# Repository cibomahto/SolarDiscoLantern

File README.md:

Solar Disco Lantern
===================

A disco twist on the traditional solar lantern, this little guy will light your way at night, and bounce to your music!

An all-analog circuit makes for a low-power and low-cost design.

The solar charging circuit is based on the Kimono Lantern Kit by Akiba:
http://www.tokyohackerspace.org/en/project/kimono-lantern

Designed by Honghong and Matt for Dragon Burn 2014

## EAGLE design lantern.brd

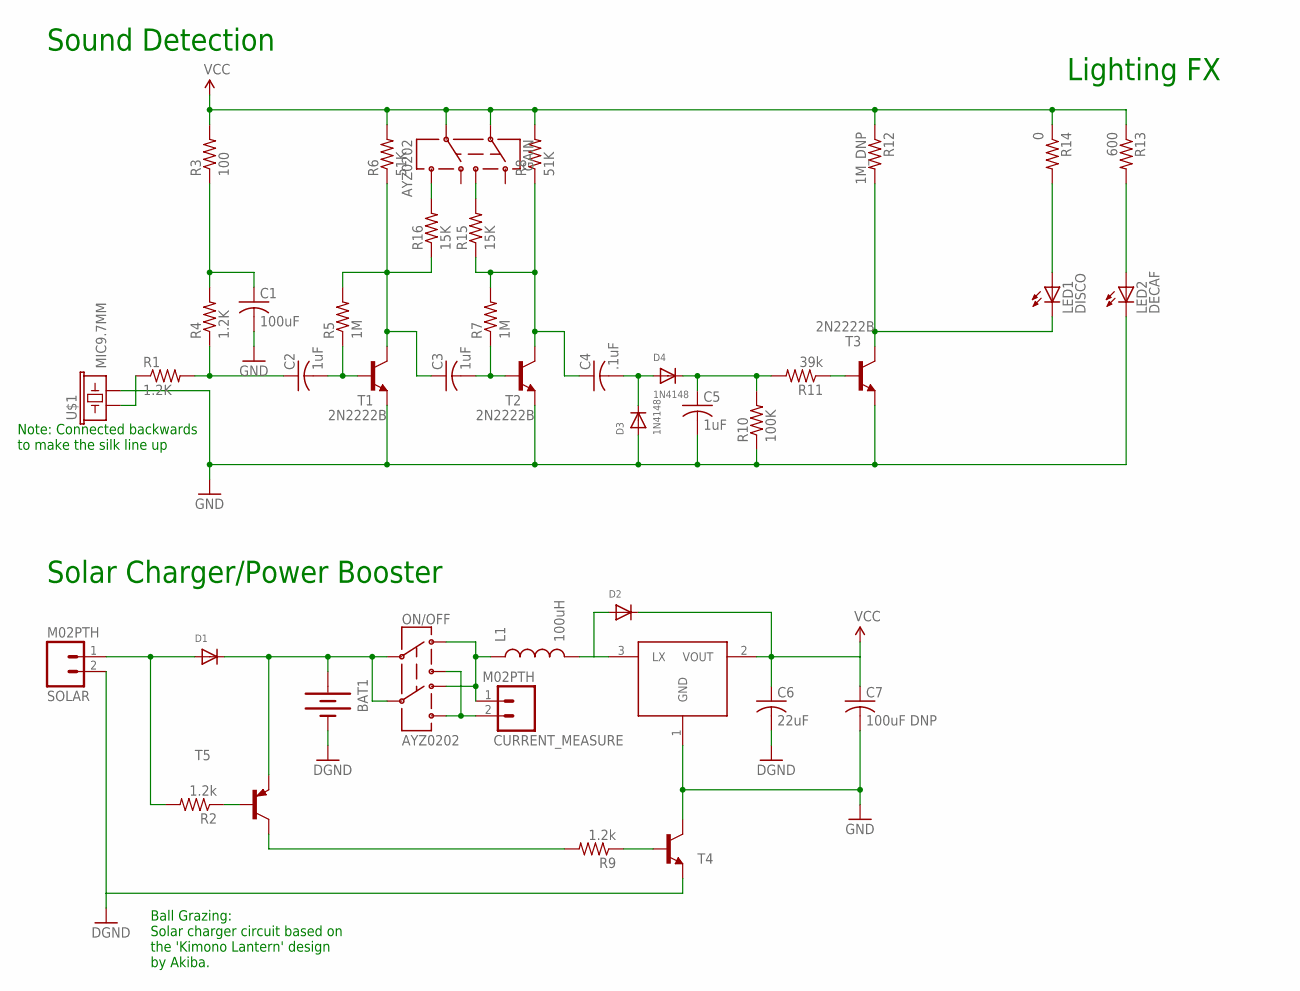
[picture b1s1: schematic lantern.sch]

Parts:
BAT1: BATTERYAAA; BATTERY-AAA
C1: 100uF; C1210
C2, C3, C5: 1uF; C0603
C4: .1uF; C0603
C6: 22uF; C0603
C7: 100uF DNP; C1210
CURRENT_MEASURE: M02PTH; 1X02
D1, D2: DIODESOT23_REFLOW; SOT23-R
D3, D4: 1N4148; SOT23-R
GAIN: AYZ0202
L1: 100uH; 0805
LED1: DISCO; LED5MM
LED2: DECAF; LED5MM
ON/OFF: AYZ0202
R1, R4: 1.2K; R0603
R2, R9: 1.2k; R0603
R3: 100; R0603
R5, R7: 1M; R0603
R6, R8: 51K; R0603
R10: 100K; R0603
R11: 39k; R0603
R12: 1M_DNP; R0603
R13: 600; R0603
R14: 0; R0603
R15, R16: 15K; R0603
SOLAR: M02PTH; 1X02
T1, T2, T3, T4: 2N2222B; SOT23
T5: 2N2907B; SOT23
U2: HT7733A; SOT89
U$1: MIC9.7MM; MIC-9.7MM

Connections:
DGND: BAT1.GND@1 (-), C6.2, SOLAR.2, T4.2 (E)
GND: C1.2, C5.2, C7.2, D3.1 (A), LED2.K (C), R10.1, T1.2 (E), T2.2 (E), T3.2 (E), T4.3 (C), U2.1 (GND), U$1.2
unnamed: C2.1, R1.2, R4.1
unnamed: C1.1, R3.1, R4.2
unnamed: C2.2, R5.1, T1.1 (B)
unnamed: C3.1, R5.2, R6.1, R16.1, T1.3 (C)
unnamed: C4.1, R7.2, R8.1, R15.1, T2.3 (C)
unnamed: C3.2, R7.1, T2.1 (B)
unnamed: R1.1, U$1.1
unnamed: LED1.K (C), R12.2, T3.3 (C)
unnamed: R11.1, T3.1 (B)
unnamed: C4.2, D3.3 (C), D4.1 (A)
unnamed: D1.1 (A), R2.2, SOLAR.1
unnamed: C5.1, D4.3 (C), R10.2, R11.2
unnamed: R9.2, T5.3 (C)
unnamed: R9.1, T4.1 (B)
unnamed: BAT1.PWR@1 (+), D1.3 (C), ON/OFF.2, ON/OFF.5, T5.2 (E)
unnamed: R2.1, T5.1 (B)
unnamed: CURRENT_MEASURE.1, L1.1, ON/OFF.3 (1), ON/OFF.6 (4)
unnamed: D2.1 (A), L1.2, U2.3 (LX)
unnamed: LED2.A, R13.2
unnamed: LED1.A, R14.2
unnamed: CURRENT_MEASURE.2, ON/OFF.1 (3), ON/OFF.4 (6)
unnamed: GAIN.4 (6), R16.2
unnamed: GAIN.1 (3), R15.2
VCC: C6.1, C7.1, D2.3 (C), GAIN.2, GAIN.5, R3.2, R6.2, R8.2, R12.1, R13.1, R14.1, U2.2 (VOUT)

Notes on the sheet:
Solar Charger/Power Booster
Sound Detection
Lighting FX
Ball Grazing: Solar charger circuit based on the 'Kimono Lantern' design by Akiba.
Note: Connected backwards to make the silk line up

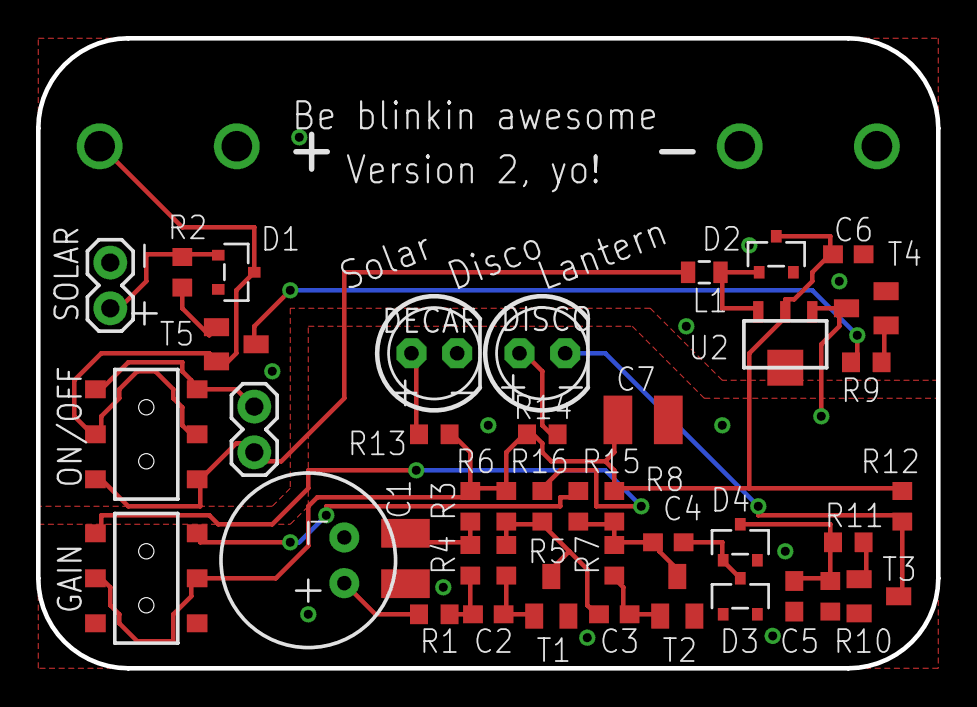
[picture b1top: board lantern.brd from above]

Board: 2 copper layers, 50.0 x 35.0 mm, 42 parts (0 on the bottom side), 26 nets.

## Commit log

2014-05-23 Add lantern
2014-05-24 RevA pcb finished, first case version
2014-05-26 Add BOM and solidwords drawing for case
2014-05-31 Small updates for RevB, change capacitor size and fix some labels. Hope it works!

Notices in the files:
parts and their libraries:
SparkFun-Connectors: Licensing: CC v3.0 Share-Alike You are welcome to use this library for commercial purposes.
